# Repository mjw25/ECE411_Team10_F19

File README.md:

# ECE411_Team10_F19
Practicum Project for ECE411 at PSU, Team 10, Fall 2019

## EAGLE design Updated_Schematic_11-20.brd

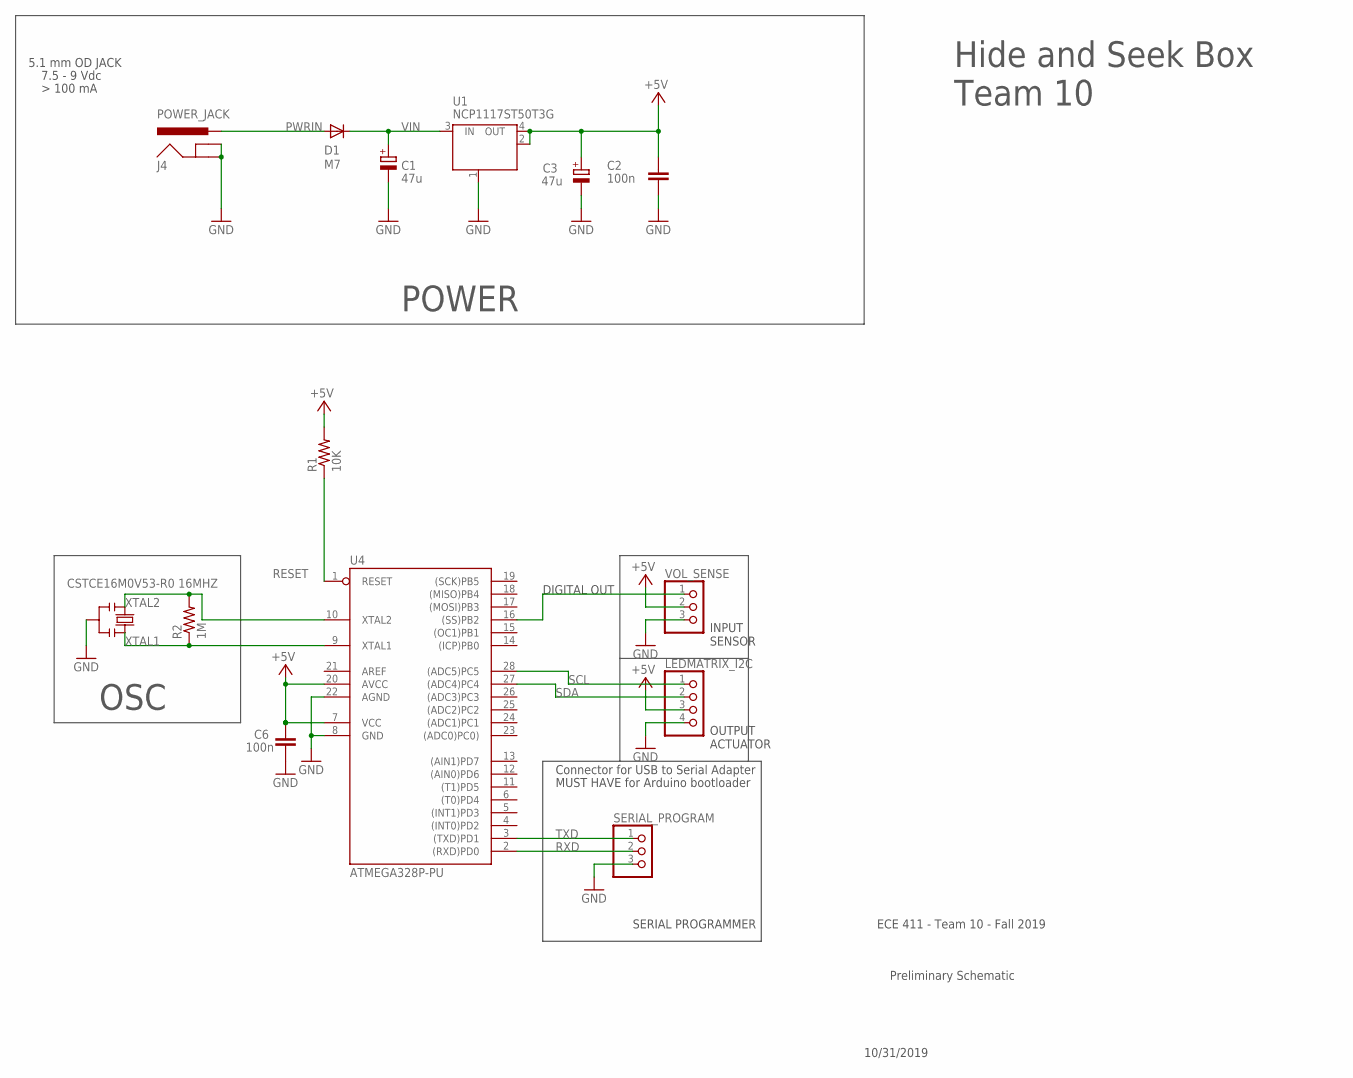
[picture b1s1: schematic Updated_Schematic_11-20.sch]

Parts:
C1, C3: 47u; PANASONIC_D
C2, C6: 100n; C0805
D1: M7; SMB
J4: POWER_JACK; POWER_JACK_PTH
LEDMATRIX_I2C: PINHD-1X4; 1X04
R1: 10K; R0805
R2: 1M; R0805
SERIAL_PROGRAM: PINHD-1X3; 1X03
U1: NCP1117ST50T3G; SOT223
U4: ATMEGA328P-PU; DIL28-3
VOL_SENSE: PINHD-1X3; 1X03
X1: CSTCE16M0V53-R0 16MHZ; RESONATOR

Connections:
+5V: C2.2, C3.+, C6.2, LEDMATRIX_I2C.3, R1.2, U1.2 (OUT), U1.4 (OUT), U4.7 (VCC), U4.20 (AVCC), VOL_SENSE.2
GND: C1.-, C2.1, C3.-, C6.1, J4.GND, J4.GNDBREAK, LEDMATRIX_I2C.4, SERIAL_PROGRAM.3, U1.1 (GND/ADJ), U4.8 (GND), U4.22 (AGND), VOL_SENSE.3, X1.2
unnamed: U4.16 ((SS)PB2), VOL_SENSE.1
PWRIN: D1.A, J4.PWR
RESET: R1.1, U4.1 (RESET)
RXD: SERIAL_PROGRAM.2, U4.2 ((RXD)PD0)
SCL: LEDMATRIX_I2C.1, U4.28 ((ADC5)PC5)
SDA: LEDMATRIX_I2C.2, U4.27 ((ADC4)PC4)
TXD: SERIAL_PROGRAM.1, U4.3 ((TXD)PD1)
VIN: C1.+, D1.C, U1.3 (IN)
XTAL1: R2.1, U4.9 (XTAL1), X1.3
XTAL2: R2.2, U4.10 (XTAL2), X1.1

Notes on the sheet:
7.5 - 9 Vdc
POWER
OSC
5.1 mm OD JACK
Connector for USB to Serial Adapter
MUST HAVE for Arduino bootloader
DIGITAL OUT
SERIAL PROGRAMMER
INPUT SENSOR
OUTPUT ACTUATOR
Preliminary Schematic
10/31/2019
ECE 411 - Team 10 - Fall 2019
Hide and Seek Box Team 10

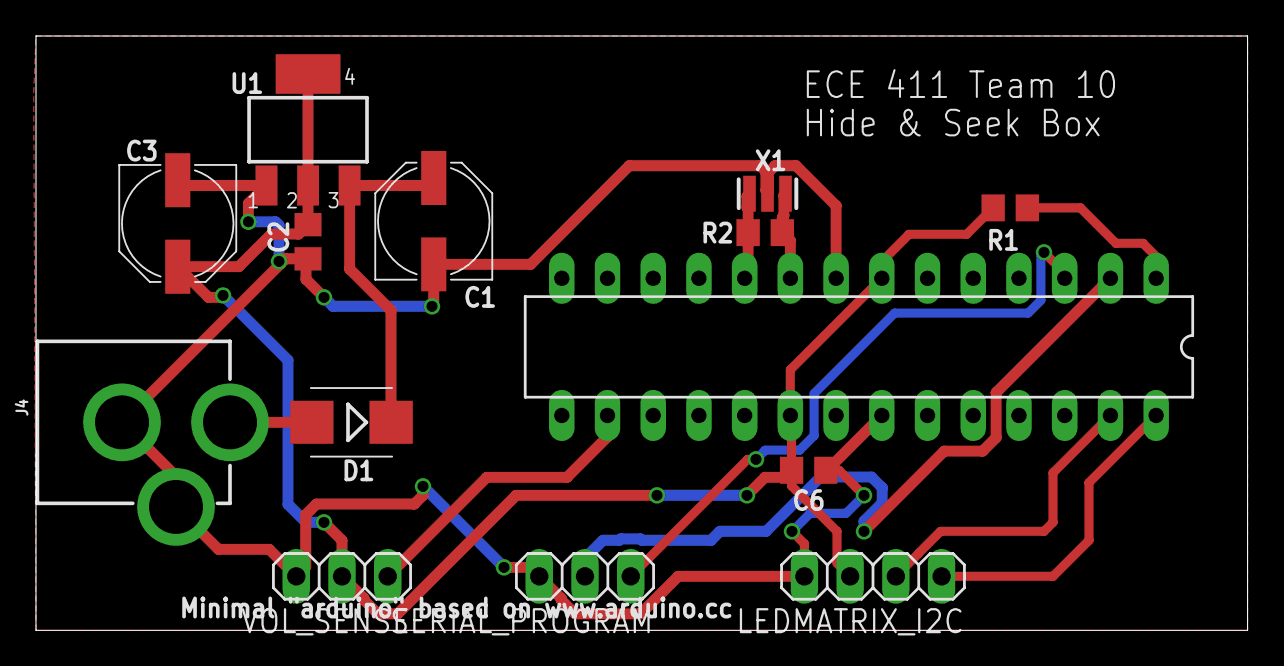
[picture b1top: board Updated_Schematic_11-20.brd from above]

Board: 2 copper layers, 67.3 x 33.0 mm, 14 parts (0 on the bottom side), 12 nets.

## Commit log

2019-10-31 Initial Breadboard Code
    This file has the code used to test the sensor and actuator using an Atmega328P Development board with Arduino Bootloader. This code allows the Atmega328P to take an Analog input from a sound volume 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
2019-11-20 Add files via upload
    Newest schematic and board for OSH Park upload
2019-12-12 Code

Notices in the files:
parts and their libraries:
SparkFun-Connectors: Licensing: Creative Commons ShareAlike 4.0 International - https://creativecommons.org/licenses/by-sa/4.0
